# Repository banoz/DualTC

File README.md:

## Dual MAX31855K board with SC18IS600IPW SPI to I2C bridge

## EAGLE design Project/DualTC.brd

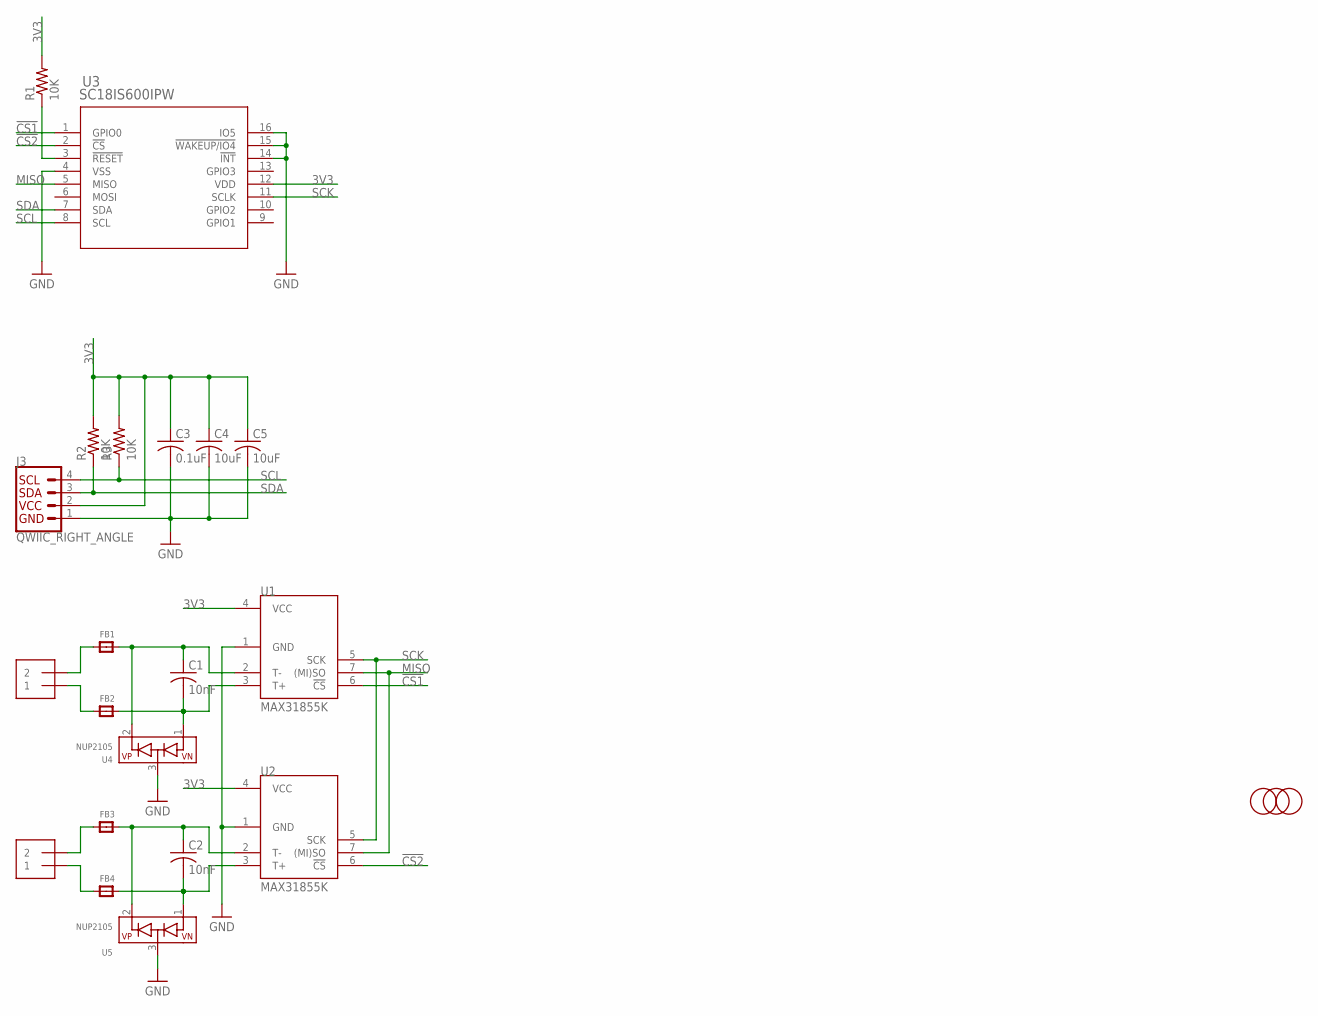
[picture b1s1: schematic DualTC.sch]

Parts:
C1, C2: 10nF; C0603; LCSC C100042
C3: 0.1uF; C0603; LCSC C14663
C4, C5: 10uF; C0603; LCSC C86275
FB1, FB2, FB3, FB4: FERRITE; 0603; LCSC C883591
J1, J2: 1X2-3.5MM; LCSC C474892
J3: QWIIC_RIGHT_ANGLE; JST04_1MM_RA; LCSC C145956
R1, R2, R3: 10K; R0603; LCSC C98220
U1, U2: MAX31855K; SO08; LCSC C52028
U3: SC18IS600IPW; SOT403-1_NXP; LCSC C2678047
U4, U5: NUP2105; SOT23-WIDE; LCSC C920312
U$1, U$2, U$3: FIDUCIAL; FIDUCIAL_1MM

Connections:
3V3: C3.1, C4.1, C5.1, J3.2, R1.2, R2.2, R3.2, U1.4 (VCC), U2.4 (VCC), U3.12 (VDD)
!CS1: U1.6 (!CS), U3.1 (GPIO0)
!CS2: U2.6 (!CS), U3.2 (!CS)
GND: C3.2, C4.2, C5.2, J3.1, U1.1 (GND), U2.1 (GND), U3.4 (VSS), U3.14 (!INT), U3.15 (!WAKEUP/IO4), U3.16 (IO5), U4.3 (IO), U5.3 (IO)
MISO: U1.7 ((MI)SO), U2.7 ((MI)SO), U3.5 (MISO)
unnamed: FB3.1, J2.2
unnamed: FB4.1, J2.1
unnamed: C2.1, FB3.2, U2.2 (T-), U5.2 (SUPPLYPIN)
unnamed: C2.2, FB4.2, U2.3 (T+), U5.1 (GNDPIN)
unnamed: FB1.1, J1.2
unnamed: C1.1, FB1.2, U1.2 (T-), U4.2 (SUPPLYPIN)
unnamed: FB2.1, J1.1
unnamed: C1.2, FB2.2, U1.3 (T+), U4.1 (GNDPIN)
unnamed: R1.1, U3.3 (!RESET)
SCK: U1.5 (SCK), U2.5 (SCK), U3.11 (SCLK)
SCL: J3.4, R3.1, U3.8 (SCL)
SDA: J3.3, R2.1, U3.7 (SDA)

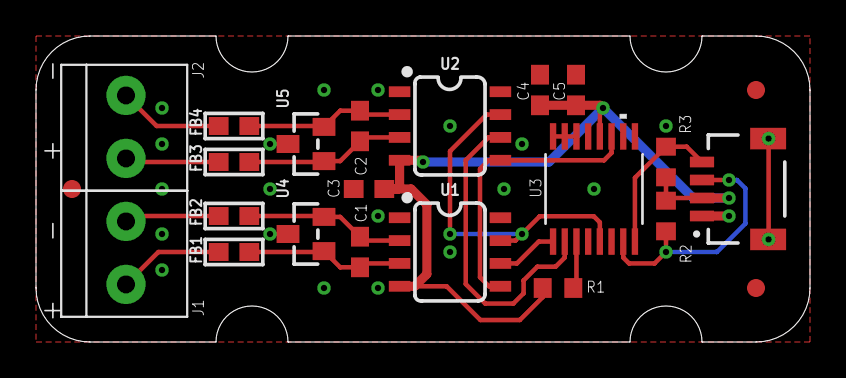
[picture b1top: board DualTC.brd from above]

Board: 2 copper layers, 43.0 x 17.0 mm, 24 parts (1 on the bottom side), 17 nets.

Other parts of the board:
U$4: QWIIC_3MM

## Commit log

2022-11-10 Create LICENSE.md
    https://ohwr.org/cern_ohl_p_v2.txt

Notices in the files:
parts and their libraries:
microbuilder: This work is placed in the public domain, and may be freely used for commercial and non-commercial work with the following conditions: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
SparkFun-Connectors: Licensing: Creative Commons ShareAlike 4.0 International - https://creativecommons.org/licenses/by-sa/4.0
